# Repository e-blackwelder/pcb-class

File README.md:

# pcb-class
project files for a PCB class

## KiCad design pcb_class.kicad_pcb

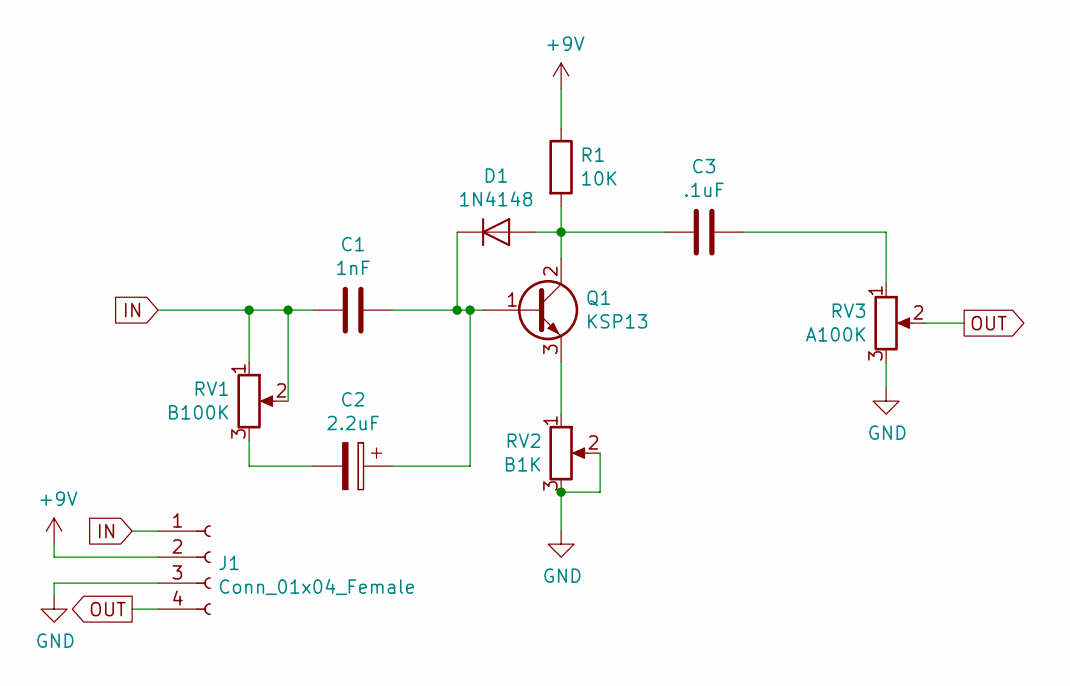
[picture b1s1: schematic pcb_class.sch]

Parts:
C1: 1nF; C_Disc_D9.0mm_W5.0mm_P7.50mm
C2: 2.2uF; CP_Radial_D5.0mm_P2.00mm
C3: .1uF; C_Rect_L7.2mm_W2.5mm_P5.00mm_FKS2_FKP2_MKS2_MKP2
D1: 1N4148; D_DO-35_SOD27_P7.62mm_Horizontal
J1: Conn_01x04_Female; PinSocket_1x04_P2.54mm_Vertical
Q1: KSP13; TO-92_Inline
R1: 10K; R_Axial_DIN0207_L6.3mm_D2.5mm_P10.16mm_Horizontal
RV1: B100K; PinSocket_1x03_P2.54mm_Vertical
RV2: B1K; PinSocket_1x03_P2.54mm_Vertical
RV3: A100K; PinSocket_1x03_P2.54mm_Vertical

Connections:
+9V: J1.2, R1.1
GND: J1.3, RV2.2, RV2.3, RV3.3
IN: C1.2, J1.1, RV1.1, RV1.2
unnamed: C1.1, C2.1, D1.1 (K), Q1.1 (B)
unnamed: C2.2, RV1.3
unnamed: C3.1, D1.2 (A), Q1.2 (C), R1.2
unnamed: C3.2, RV3.1
unnamed: Q1.3 (E), RV2.1
OUT: J1.4, RV3.2

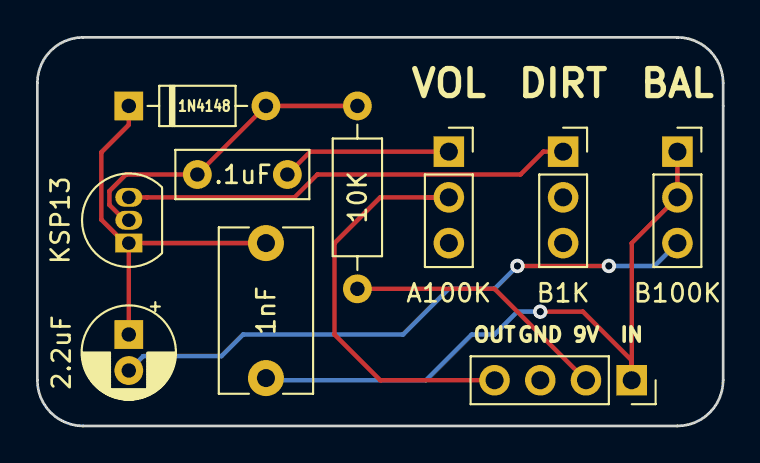
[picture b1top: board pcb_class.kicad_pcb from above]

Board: 2 copper layers, 38.1 x 21.6 mm, 10 parts (0 on the bottom side), 9 nets.

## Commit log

2019-10-25 Schematic created
2019-10-25 Footprints assigned, netlist generated
2019-10-25 Routed
2019-10-25 gerbers generated
